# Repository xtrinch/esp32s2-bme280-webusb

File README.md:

# esp32s2-bme280-webusb

Sends periodic `bme280` humidity, temperature, pressure and battery voltage data from `esp32s2 development board` to [sensor dashboard](http://iotfreezer.com) backend via Wi-Fi. 

Is configurable via a [web interface](http://iotfreezer.com/) using webusb. Since the board uses native usb communication, the serial output will also be emulated via USB so it may not work as you would expect a regular serial connection - if it's configured wrongly, there will be no output in your serial monitor. If the board sleeps, when you connect it to USB, you will not be able to flash it. Board needs to be wide awake and listening to USB commands for flashing to work. When the board is connected to the computer - the neopixel of the esp32s2 will light up and the display should display `PC` instead of the usual measurements.

If you botch the code and manage to put it to sleep when on USB, boot the board into bootloader mode by holding the button `BUT1` on the board when connecting to USB, then you will be able to flash via USB again.

Currently, this firmware can make it around 7 months on a 1200mA battery connected to the dev board. The board can be configured to send the measurements to the server once every N times via the parameter `maxRtcRecords` to optimize battery time.

Built with PlatformIO.

See also [backend](https://github.com/xtrinch/sensor-dashboard-nestjs-backend) and [frontend](https://github.com/xtrinch/sensor-dashboard-react-frontend) repo, or [see it live](http://iotfreezer.com/) with some sensor data from my living room.

## Components
- ESP32S2 dev board with native usb support, meaning there should not be a usb to serial converter on the board, I used [ESP32-S2-DevKit-Lipo-USB from Olimex](https://www.olimex.com/Products/IoT/ESP32-S2/ESP32-S2-DevKit-Lipo-USB/open-source-hardware)
- Waveshare e-paper 1.54inch display - black and white version
- Bosch BME280 sensor module
- 3.7V LiPo battery (or other), e.g. [BATTERY-LIPO1400mAh from Olimex](https://www.olimex.com/Products/Power/BATTERY-LIPO1400mAh/)

## Additional things needed to assemble the PCB
- PH2.0 8 pin connectors for the display (bent needle for the PCB)
- min 2, max 4 2.0mm high spacers to mount the display above the ESP32S2, depending on how many sides of the display you want to fixate
- PH2.0 2pin connector for the battery (if the battery doesn't already come with one)
- bunch of male / female headers
- 1x push button - right angled for RESET button
- 1x push button - regular for BOOT button

## Setup

1. Have a sensor dashboard backend running (see https://github.com/xtrinch/sensor-dashboard-nestjs-backend) or use [iotfreezer](http://iotfreezer.com/).
2. remove the solder from `LED1_ENABLE SMD` jumper (i.e. open it) on the ESP32S2, because it consumes a large current 
3. solder the `BAT_SENS` and `PWR_SENS` jumpers on the ESP32S2, to be able to detect battery voltage levels
4. Uncomment the part in `main.cpp` that routes VREF to a GPIO on the ESP32S2. Program the board, measure VREF and input it into `import_env.py` under `REF_VOLTAGE` (if it's e.g. 1.1, input 1100). This will be needed for accurate battery measurement and you cannot skip this step.
5. Copy `import_env.example.py` to `import_env.py` and define your sensor dashboard url.
6. Run `pio run -t buildfs && pio run -t uploadfs` to upload the icons the display uses for humidity/temperature
7. While having your board plugged into the computer, reboot the board and configure it via the web interface (via webusb) of the sensor dashboard (iotfreezer).

## Troubleshooting

If you cannot upload to your board on linux, input `sudo chmod a+rw /dev/ttyUSB0`.

To monitor across reboots, as uploading and monitoring does not work, use the following command on Linux:
`while [ true ]; do cat /dev/ttyACM0; done`
 
To check out the usb descriptors, run `lsusb -v`. To check out the kernel logs for errors, run `dmesg`.
## Convert icons

 `convert temperature-2-48.png -background white -alpha remove -alpha off -compress none -depth 24 -resize 48x48 temp-final.bmp`

## Production deploy

Make sure to turn off `DEBUG` to save power.

## PCB

See `schematics-w-display` folder for full project. It was drawn in KiCad and it's a two sided PCB.

## End product with casing

Casing is parametric and drawn in FreeCad 0.19. It is made to fit the above PCB. For FreeCad project, see `casing-w-display` folder.

# TODOs
- use ULP to use power pin as ADC wakeup source
- reference ADC voltage to parametrizable params?

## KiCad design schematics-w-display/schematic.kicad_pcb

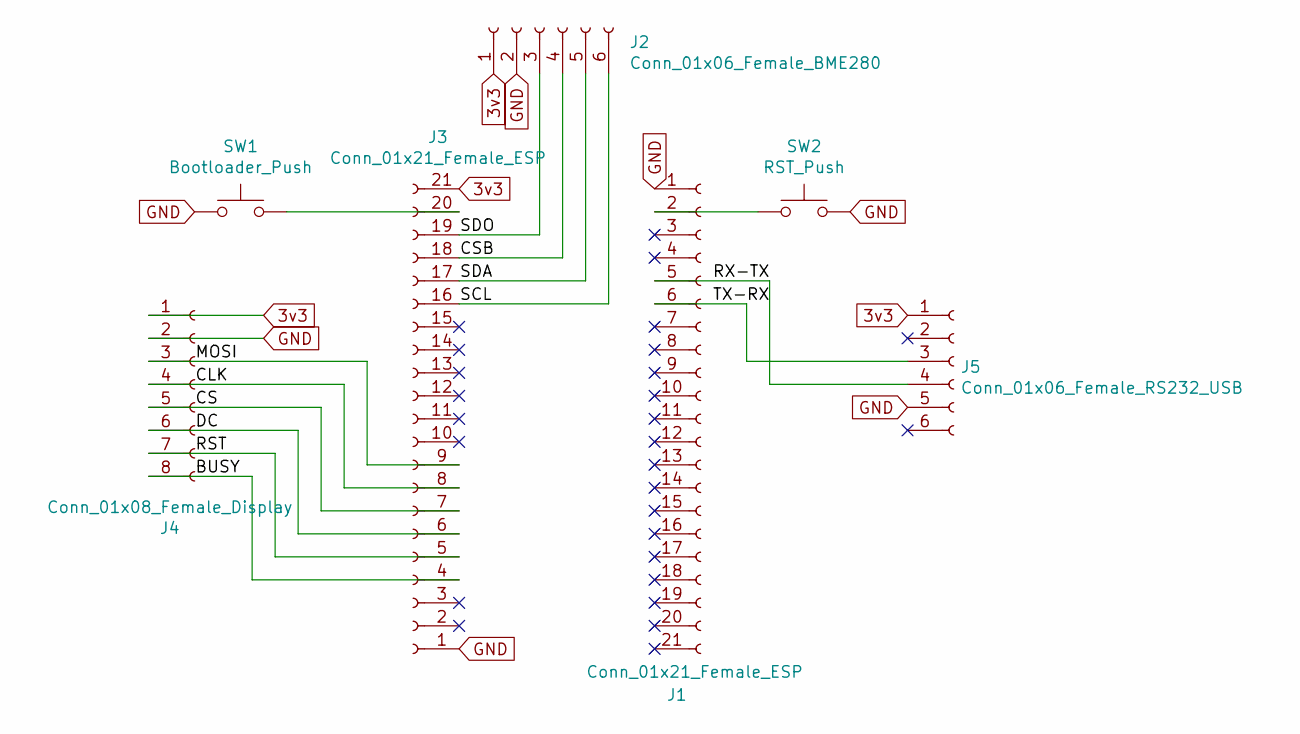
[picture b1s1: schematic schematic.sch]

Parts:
J1, J3: Conn_01x21_Female_ESP; PinHeader_1x21_P2.54mm_Vertical
J2: Conn_01x06_Female_BME280; PinHeader_1x06_P2.54mm_Vertical
J4: Conn_01x08_Female_Display; JST_PH_S8B-PH-K_1x08_P2.00mm_Horizontal
J5: Conn_01x06_Female_RS232_USB; PinHeader_1x06_P2.54mm_Vertical
SW1: Bootloader_Push; SW_PUSH_6mm
SW2: RST_Push; SW_Tactile_SKHH_Angled

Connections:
3v3: J2.1, J3.21, J4.1, J5.1
/BUSY: J3.4, J4.8
/CLK: J3.8, J4.4
/CS: J3.7, J4.5
/CSB: J2.4, J3.18
/DC: J3.6, J4.6
/MOSI: J3.9, J4.3
/RST: J3.5, J4.7
/RX-TX: J1.5, J5.4
/SCL: J2.6, J3.16
/SDA: J2.5, J3.17
/SDO: J2.3, J3.19
/TX-RX: J1.6, J5.3
GND: J1.1, J2.2, J3.1, J4.2, J5.5, SW1.1, SW2.2
unnamed: J1.2, SW2.1
unnamed: J3.20, SW1.2

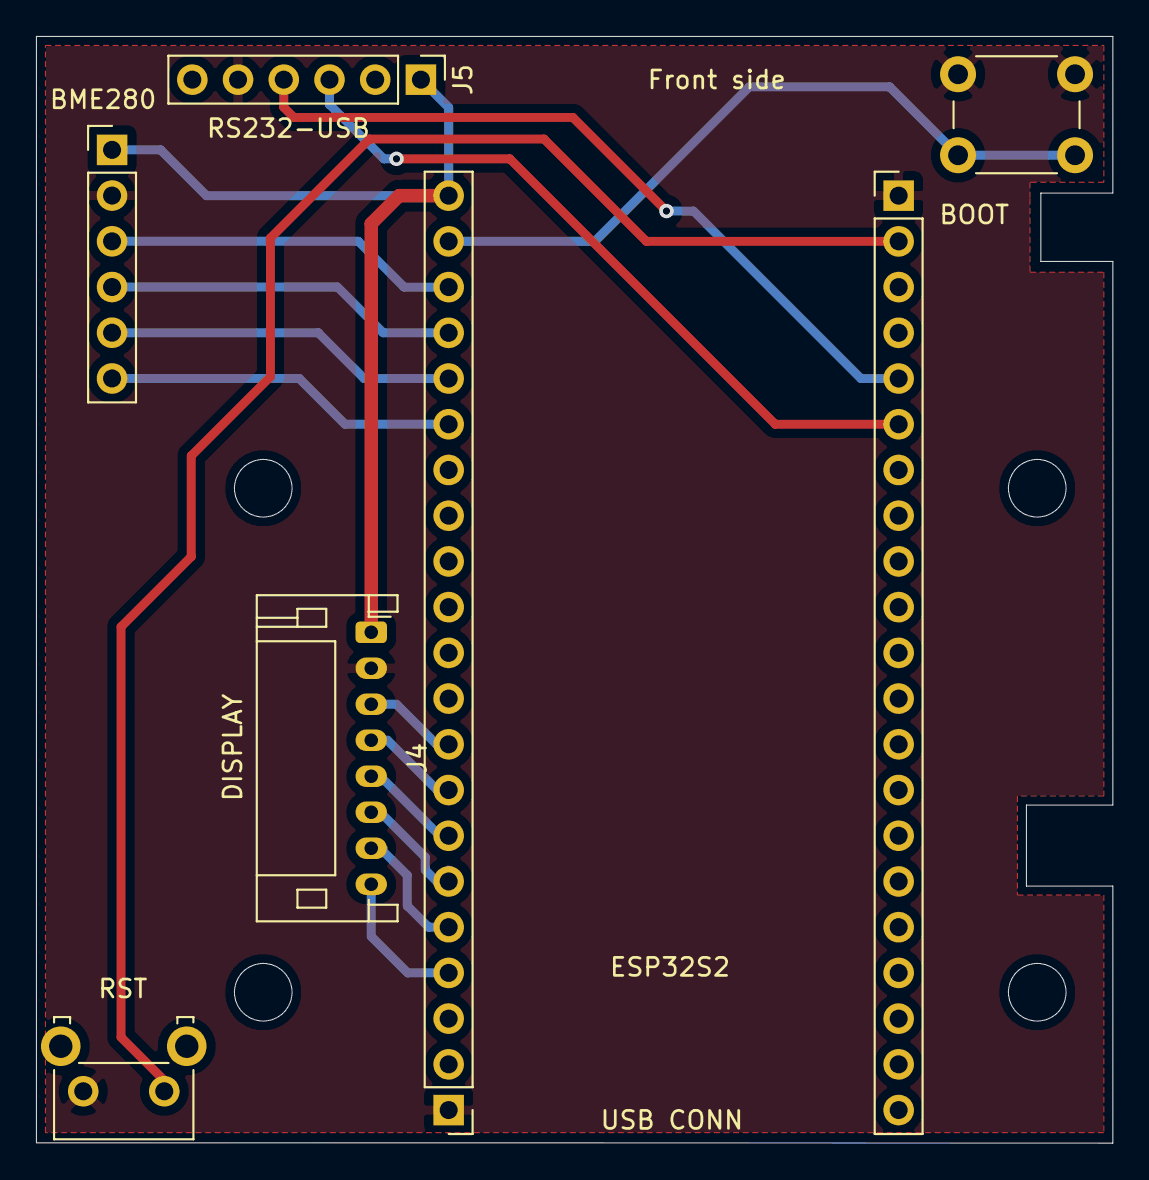
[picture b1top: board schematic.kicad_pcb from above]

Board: 2 copper layers, 59.8 x 61.5 mm, 10 parts (0 on the bottom side), 16 nets.

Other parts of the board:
 : MountingHole_3.2mm_M3_DIN965
 #2,  #3: MountingHole_3.2mm_M3_DIN965

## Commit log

2020-10-01 Udpate image link
2020-10-11 Send to https
2020-10-11 HTTPS support
2020-10-11 I2c address to cfg
2020-10-11 Certificate
2021-01-06 Esp32s2 support, I2C->SPI
2021-02-03 Change frequency to 80mhz
2021-03-07 Debug variable added
2021-03-11 RTC memory
2021-03-13 Add schematics for ESP32S2
2021-03-19 Kicad schematics
2021-04-19 Some stuff
2021-04-19 Remove old schematics
2021-04-19 EEPROM Addresses bugfixes; working version
2021-04-19 Bump esp make easy version
2021-04-20 Do not stay awake after first batch sent
2021-04-28 Some comments
2021-05-05 Update branch of arduino-esp23 as alpha support for esp32s2 has been added
2021-05-07 EEPROM->preferences
2021-05-08 Cleanup
2021-05-08 Working version of preferences
2021-05-08 Some battery sensing code
2021-05-10 Send battery to server
2021-05-10 Fix battery calibration value
2021-05-10 Fix json size
2021-05-10 Remove the lib
2021-05-27 First attempt
2021-05-27 Works but is faded
2021-05-27 GxEPD2 working
2021-05-27 Success
2021-05-27 Partial refresh works!
2021-05-27 Still works
2021-05-27 Add picture
2021-05-27 Draw marilyn
2021-06-06 Some basic screen design
2021-06-07 Update battery sensing measurements
2021-06-07 ADC calibration: success
2021-06-11 Battery indicator
2021-07-11 Use own platformio branch
2021-07-11 Initial version of schematics
2021-07-11 Version 2
2021-07-13 Final version
2021-07-14 Maybe not so final version
2021-07-14 Final version: again
2021-07-16 Final
2021-07-29 Working version, no USB work
2021-07-29 Some cleanup
2021-07-29 Worksss
2021-07-30 PSRAM flag
2021-07-30 Works again
2021-08-01 Power indicator: works
2021-08-02 Update esptinyusb link
2021-08-06 Fix battery percentage display
2021-09-03 Some schematic prettify
2021-09-03 Add LDR to schematic
2021-09-03 Use resistor as footprint for resistor
2022-02-28 Remove 20 second delay after update display
2022-03-29 Some schematic
2022-03-29 New version of display pcb
2022-04-04 Minor changes
2022-04-17 Add casing
2022-04-17 Amend readme
2022-04-20 Some more schematics
2022-04-20 Add PC conn to display
2022-04-22 Air holes + move stuff around
2022-04-23 Flat lid
2022-04-24 Boxed version: OK
2022-04-24 Minor aux fixes + display w/h
2022-04-24 Chamfer the non-printable back
2022-04-24 Further decrease display wdth
2022-04-24 V6 final
2022-04-25 After yellow print: Fix the back floating chamfer
2022-04-26 Properly handle debug turn off
2022-04-26 Add some pictures
2022-04-26 Add linguist file
2022-04-29 Casing v8
2022-04-29 Clean out some package definitions
2022-04-29 Add todos
2022-05-10 Minor fixes
2022-05-10 Fix for the new displays and hope it still works for old ones
2022-05-12 Spacers
2022-05-12 Minor readme fix
2022-05-12 Final spacer version
2022-05-13 More readme
2022-05-13 Decrease height of bo
2022-05-13 0.1 increase of box wall mount
2022-05-13 Initial print
2022-05-13 Back slider different type
2022-05-13 Fitting back
2022-05-15 Fitting back 2
2022-05-15 Fitting back 3
2022-05-15 Fitting back 4
2022-05-15 Print version
2022-05-15 Remvoe some todos
2022-05-15 Obj height -0.5mm, lid length -0.1mm
2022-05-19 Usable
2022-05-20 Tweaks
2022-05-21 Something something
2022-05-22 Fix box height
2022-05-22 Skip cloud connection when charging because readings will be off
2022-05-29 Minor cleanup
2022-06-04 Thinner version with small headers
2022-06-06 Move boot button up
2022-06-06 Add additional cable hole
2022-06-13 Remove LDR, add serial converter
2022-10-14 Some last schematic changes
2022-10-14 Put the controller to sleep when battery < 3.2
2022-10-17 Add todo
2022-10-22 Update some libs
2022-10-22 Revert to last working version of espressif32
